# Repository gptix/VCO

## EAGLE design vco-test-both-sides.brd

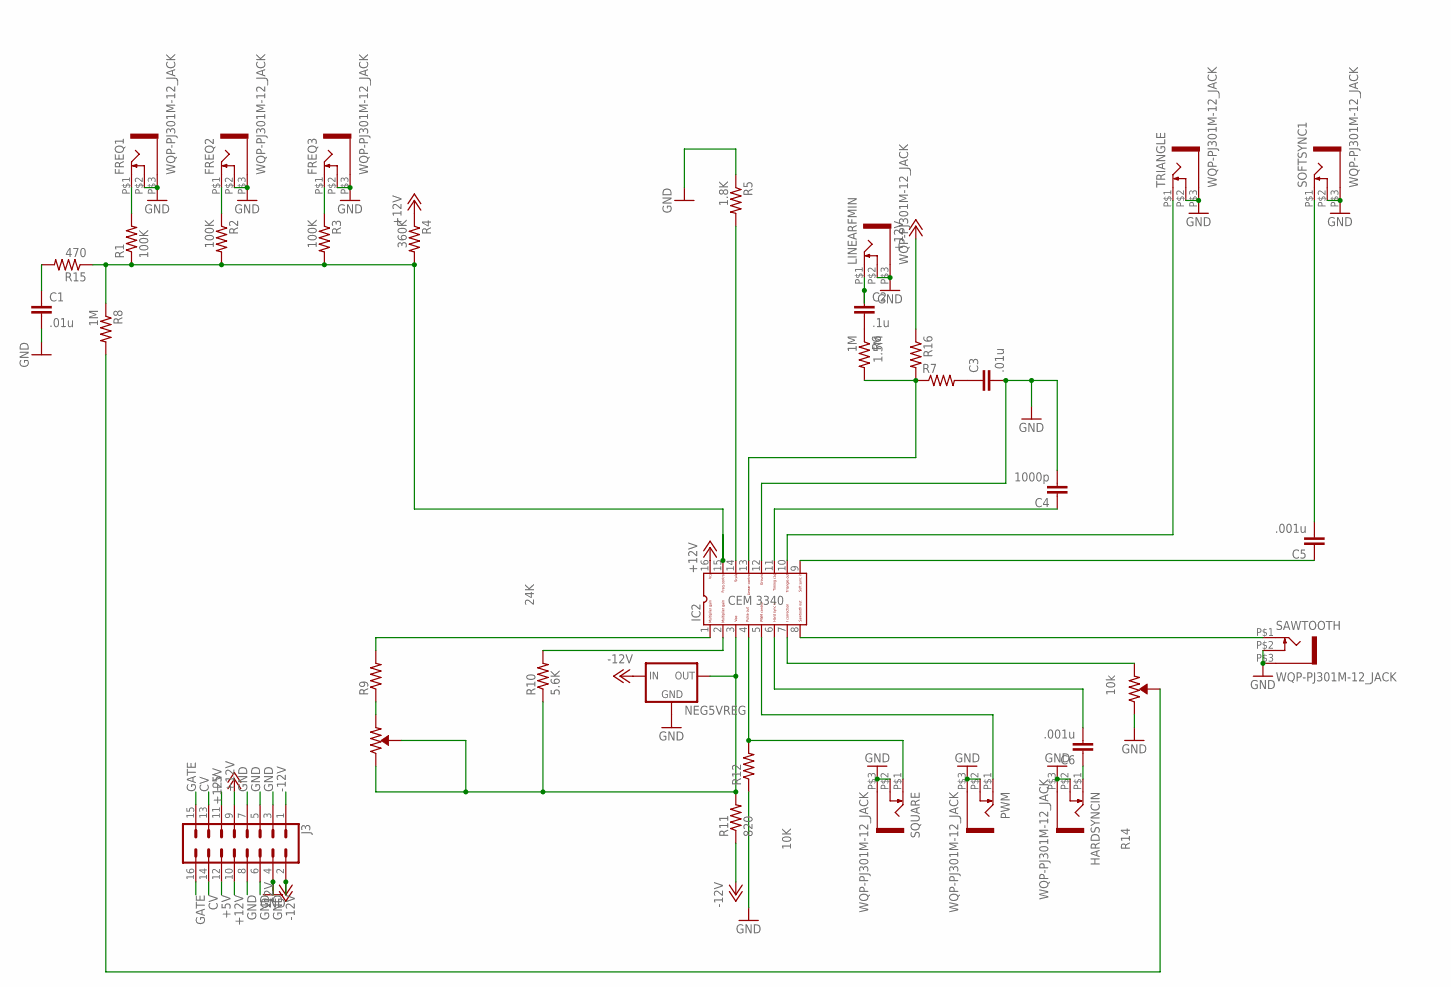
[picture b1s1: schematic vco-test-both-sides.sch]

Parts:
C1, C3: .01u; C050-025X075
C2: .1u; C050-025X075
C4: 1000p; C050-025X075
C5, C6: .001u; C050-025X075
FREQ1, FREQ2, FREQ3: WQP-PJ301M-12_JACK
HARDSYNCIN: WQP-PJ301M-12_JACK
IC2: CEM3340; DIL16
J3: CONN_08X2_SHROUD; 2X8-SHROUDED_LOCK
LINEARFMIN: WQP-PJ301M-12_JACK
NEG5VREG: V_REG_78XXTO-92_UNTESTED; TO-92
PWM: WQP-PJ301M-12_JACK
R1, R2, R3: 100K; 0207/10
R4: 360K; 0207/10
R5: 1.8K; 0207/10
R6, R8: 1M; 0207/10
R7: R-US_0207/10; 0207/10
R9: 24K; 0207/10
R10: 5.6K; 0207/10
R11: 820; 0207/10
R12: 10K; 0207/10
R13, R14: 10k; TRIMPOT-PTH-3386U
R15: 470; 0207/10
R16: 1.5M; 0207/10
SAWTOOTH: WQP-PJ301M-12_JACK
SOFTSYNC1: WQP-PJ301M-12_JACK
SQUARE: WQP-PJ301M-12_JACK
TRIANGLE: WQP-PJ301M-12_JACK

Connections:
+5V: J3.11, J3.12
+12V: IC2.16, J3.9, J3.10, R4.1, R16.1
-12V: J3.1, J3.2, NEG5VREG.3 (IN), R11.1
CV: J3.13, J3.14
GATE: J3.15, J3.16
GND: C3.2, C4.2, FREQ1.P$2 (3), FREQ1.P$3 (1), FREQ2.P$2 (3), FREQ2.P$3 (1), FREQ3.P$2 (3), FREQ3.P$3 (1), HARDSYNCIN.P$2 (3), HARDSYNCIN.P$3 (1), IC2.12, J3.3, J3.4, J3.5, J3.6, J3.7, J3.8, LINEARFMIN.P$2 (3), LINEARFMIN.P$3 (1), NEG5VREG.2 (GND), PWM.P$2 (3), PWM.P$3 (1), R12.1, R14.3 (CW), SAWTOOTH.P$2 (3), SAWTOOTH.P$3 (1), SOFTSYNC1.P$2 (3), SOFTSYNC1.P$3 (1), SQUARE.P$2 (3), SQUARE.P$3 (1), TRIANGLE.P$2 (3), TRIANGLE.P$3 (1)
unnamed: IC2.2, R10.2
unnamed: C1.1, R15.2
unnamed: IC2.14, R5.2
unnamed: IC2.13, R6.2, R7.1, R16.2
unnamed: C2.2, R6.1
unnamed: C3.1, R7.2
unnamed: C4.1, IC2.11
unnamed: IC2.1, R9.2
unnamed: C5.1, IC2.9
unnamed: R8.2, R14.2 (WIPER)
unnamed: R9.1, R13.1 (CCW)
unnamed: IC2.3, NEG5VREG.1 (OUT), R10.1, R11.2, R13.2 (WIPER), R13.3 (CW)
unnamed: IC2.7, R14.1 (CCW)
unnamed: FREQ1.P$1 (2), R1.2
unnamed: C6.2, IC2.6
unnamed: C6.1, HARDSYNCIN.P$1 (2)
unnamed: IC2.4, R12.2, SQUARE.P$1 (2)
unnamed: FREQ2.P$1 (2), R2.1
unnamed: IC2.15, R1.1, R2.2, R3.2, R4.2, R8.1, R15.1
unnamed: FREQ3.P$1 (2), R3.1
unnamed: IC2.10, TRIANGLE.P$1 (2)
unnamed: C2.1, LINEARFMIN.P$1 (2)
unnamed: C5.2, SOFTSYNC1.P$1 (2)
unnamed: IC2.8, SAWTOOTH.P$1 (2)
unnamed: IC2.5, PWM.P$1 (2)
PE: C1.2, R5.1

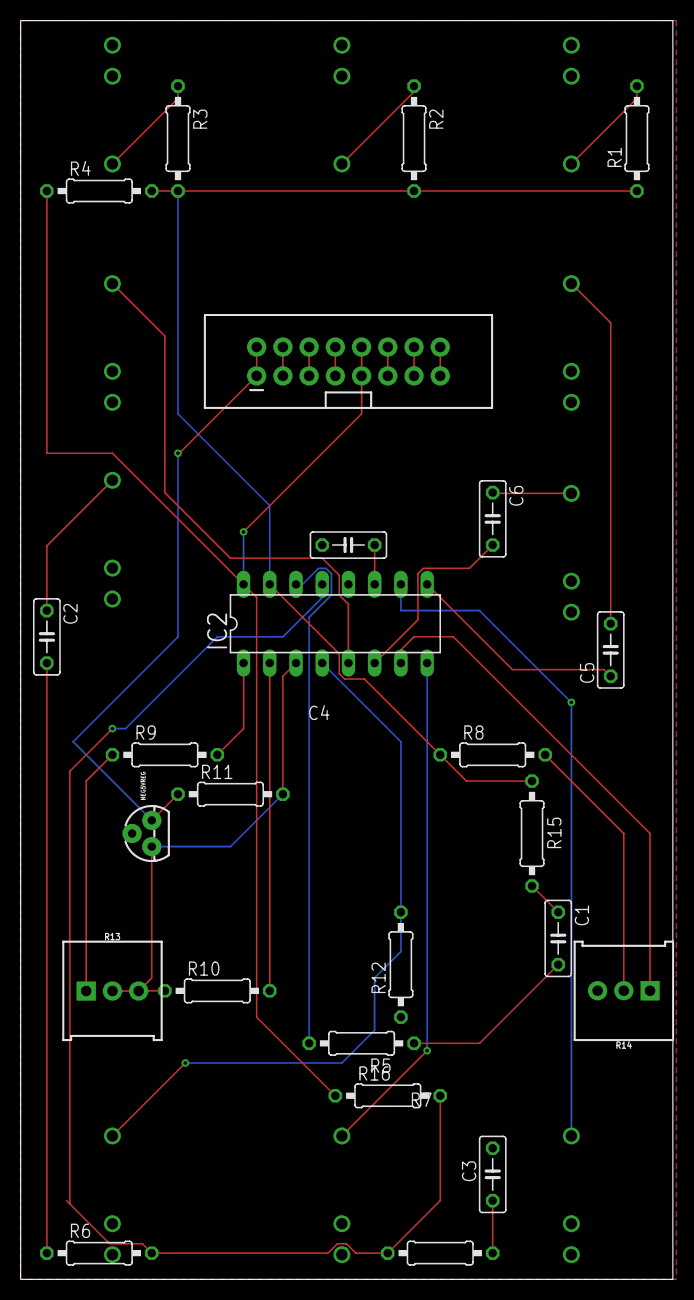
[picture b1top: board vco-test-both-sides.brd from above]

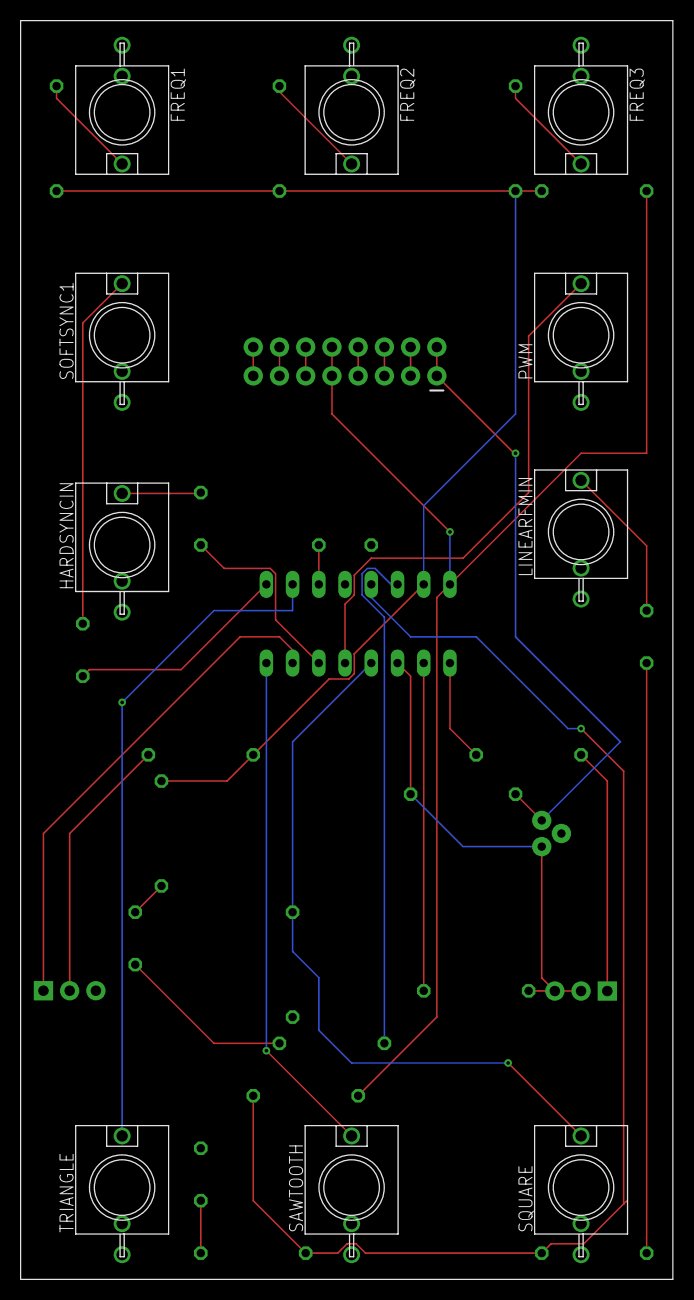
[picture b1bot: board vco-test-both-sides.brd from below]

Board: 2 copper layers, 63.2 x 121.9 mm, 35 parts (10 on the bottom side), 32 nets.

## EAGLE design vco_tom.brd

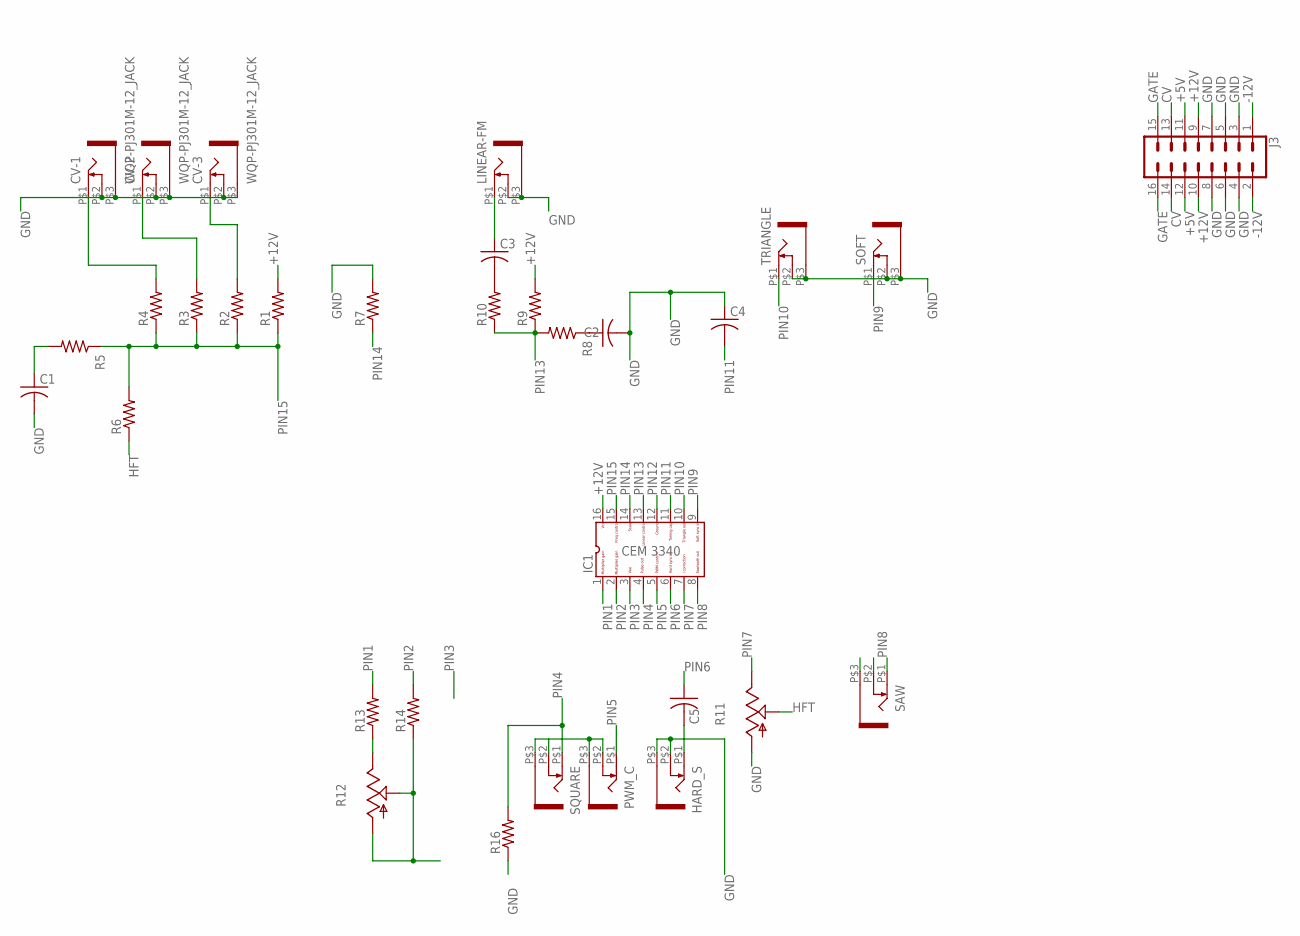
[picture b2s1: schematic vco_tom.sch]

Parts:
C1, C2, C3, C4, C5: C-US050-024X044; C050-024X044
CV-1, CV-2, CV-3: WQP-PJ301M-12_JACK
HARD_S: WQP-PJ301M-12_JACK
IC1: CEM3340; DIL16
J3: CONN_08X2_SHROUD; 2X8-SHROUDED_LOCK
LINEAR-FM: WQP-PJ301M-12_JACK
PWM_C: WQP-PJ301M-12_JACK
R1, R2, R3, R4, R5, R6, R7, R8, R9, R10, R13, R14, R16: R-US_0207/10; 0207/10
R11, R12: TRIM_US-B64Y; B64Y
SAW: WQP-PJ301M-12_JACK
SOFT: WQP-PJ301M-12_JACK
SQUARE: WQP-PJ301M-12_JACK
TRIANGLE: WQP-PJ301M-12_JACK

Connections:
+5V: J3.11, J3.12
+12V: IC1.16, J3.9, J3.10, R1.2, R9.2
-12V: J3.1, J3.2
CV: J3.13, J3.14
GATE: J3.15, J3.16
GND: C1.2, C2.2, C4.1, CV-1.P$2 (3), CV-1.P$3 (1), CV-2.P$2 (3), CV-2.P$3 (1), CV-3.P$2 (3), CV-3.P$3 (1), HARD_S.P$2 (3), HARD_S.P$3 (1), J3.3, J3.4, J3.5, J3.6, J3.7, J3.8, LINEAR-FM.P$2 (3), LINEAR-FM.P$3 (1), R7.2, R11.A, R16.1, SOFT.P$2 (3), SOFT.P$3 (1), TRIANGLE.P$2 (3), TRIANGLE.P$3 (1)
HFT: R6.1, R11.S
unnamed: C1.1, R5.2
unnamed: C3.2, R10.2
unnamed: R12.E, R13.1
unnamed: C2.1, R8.1
unnamed: CV-1.P$1 (2), R4.2
unnamed: CV-2.P$1 (2), R3.2
unnamed: C3.1, LINEAR-FM.P$1 (2)
unnamed: CV-3.P$1 (2), R2.2
unnamed: R12.A, R12.S, R14.1
unnamed: C5.2, HARD_S.P$1 (2)
unnamed: PWM_C.P$2 (3), PWM_C.P$3 (1), SQUARE.P$3 (1)
PIN1: IC1.1, R13.2
PIN2: IC1.2, R14.2
PIN3: IC1.3
PIN4: IC1.4, R16.2, SQUARE.P$1 (2)
PIN5: IC1.5, PWM_C.P$1 (2)
PIN6: C5.1, IC1.6
PIN7: IC1.7, R11.E
PIN8: IC1.8, SAW.P$1 (2)
PIN9: IC1.9, SOFT.P$1 (2)
PIN10: IC1.10, TRIANGLE.P$1 (2)
PIN11: C4.2, IC1.11
PIN12: IC1.12
PIN13: IC1.13, R8.2, R9.1, R10.1
PIN14: IC1.14, R7.1
PIN15: IC1.15, R1.1, R2.1, R3.1, R4.1, R5.1, R6.2

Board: 2 copper layers, 32 parts (0 on the bottom side), 31 nets, no tracks yet.

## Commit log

2018-12-16 Initial Commit.
2018-12-16 Added org file as notes for Tom.
2018-12-16 Added brd file, updated org file.
2018-12-17 Changed pots, added connector, updated org file.
2018-12-18 Added -5v regulator as option. fixed pin 4.
2018-12-19 Added Tom's schematic.
2018-12-20 Updated todo list. Updated form factors of capacitors.
2018-12-26 Added a new project (version), using both sides of board.
2018-12-29 Added another, smaller board design. Added PDF from Tom.

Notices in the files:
parts and their libraries:
SparkFun-IC-Power: Licensing: Creative Commons ShareAlike 4.0 International - https://creativecommons.org/licenses/by-sa/4.0
